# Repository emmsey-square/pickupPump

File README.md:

#   PickupPump- a Vacuum Pickup Tool for SMD Components (In Progress)

##  Brief

I was a big fan of the Pixel Pump project by Robbin's and loving the idea, but wanting to create my own version to better suit my needs, as well as allow me to design a circuit board of my own, I started working on my very own version. 

## Design Choices 

- RP2350 for the main mcu as it's a new and interesting chip from Raspberry Pi with a very solid SDK for built for both of the RP2X chips. 
- USB-C port for power & USB paired with a CH224K USB PD sink chip to request 12V for all of the motors/pumps and a switching converter to step-down the voltage for the mcu
- JST connector for connection to an additional PCB outfitted with a 3x2 array of pushbuttons, with each one having functions such as toggling the current suction state of the pump, increasing/decreasing suction strength, etc.
- There's 3 Sparkfun Qwiic/ Stemma Qt compatible JST connectors onboard to connect to an Adafruit I2C OLED as well as to allow for expansions (ie. footswitch)
- Onboard Cortex debug header for debugging & programming

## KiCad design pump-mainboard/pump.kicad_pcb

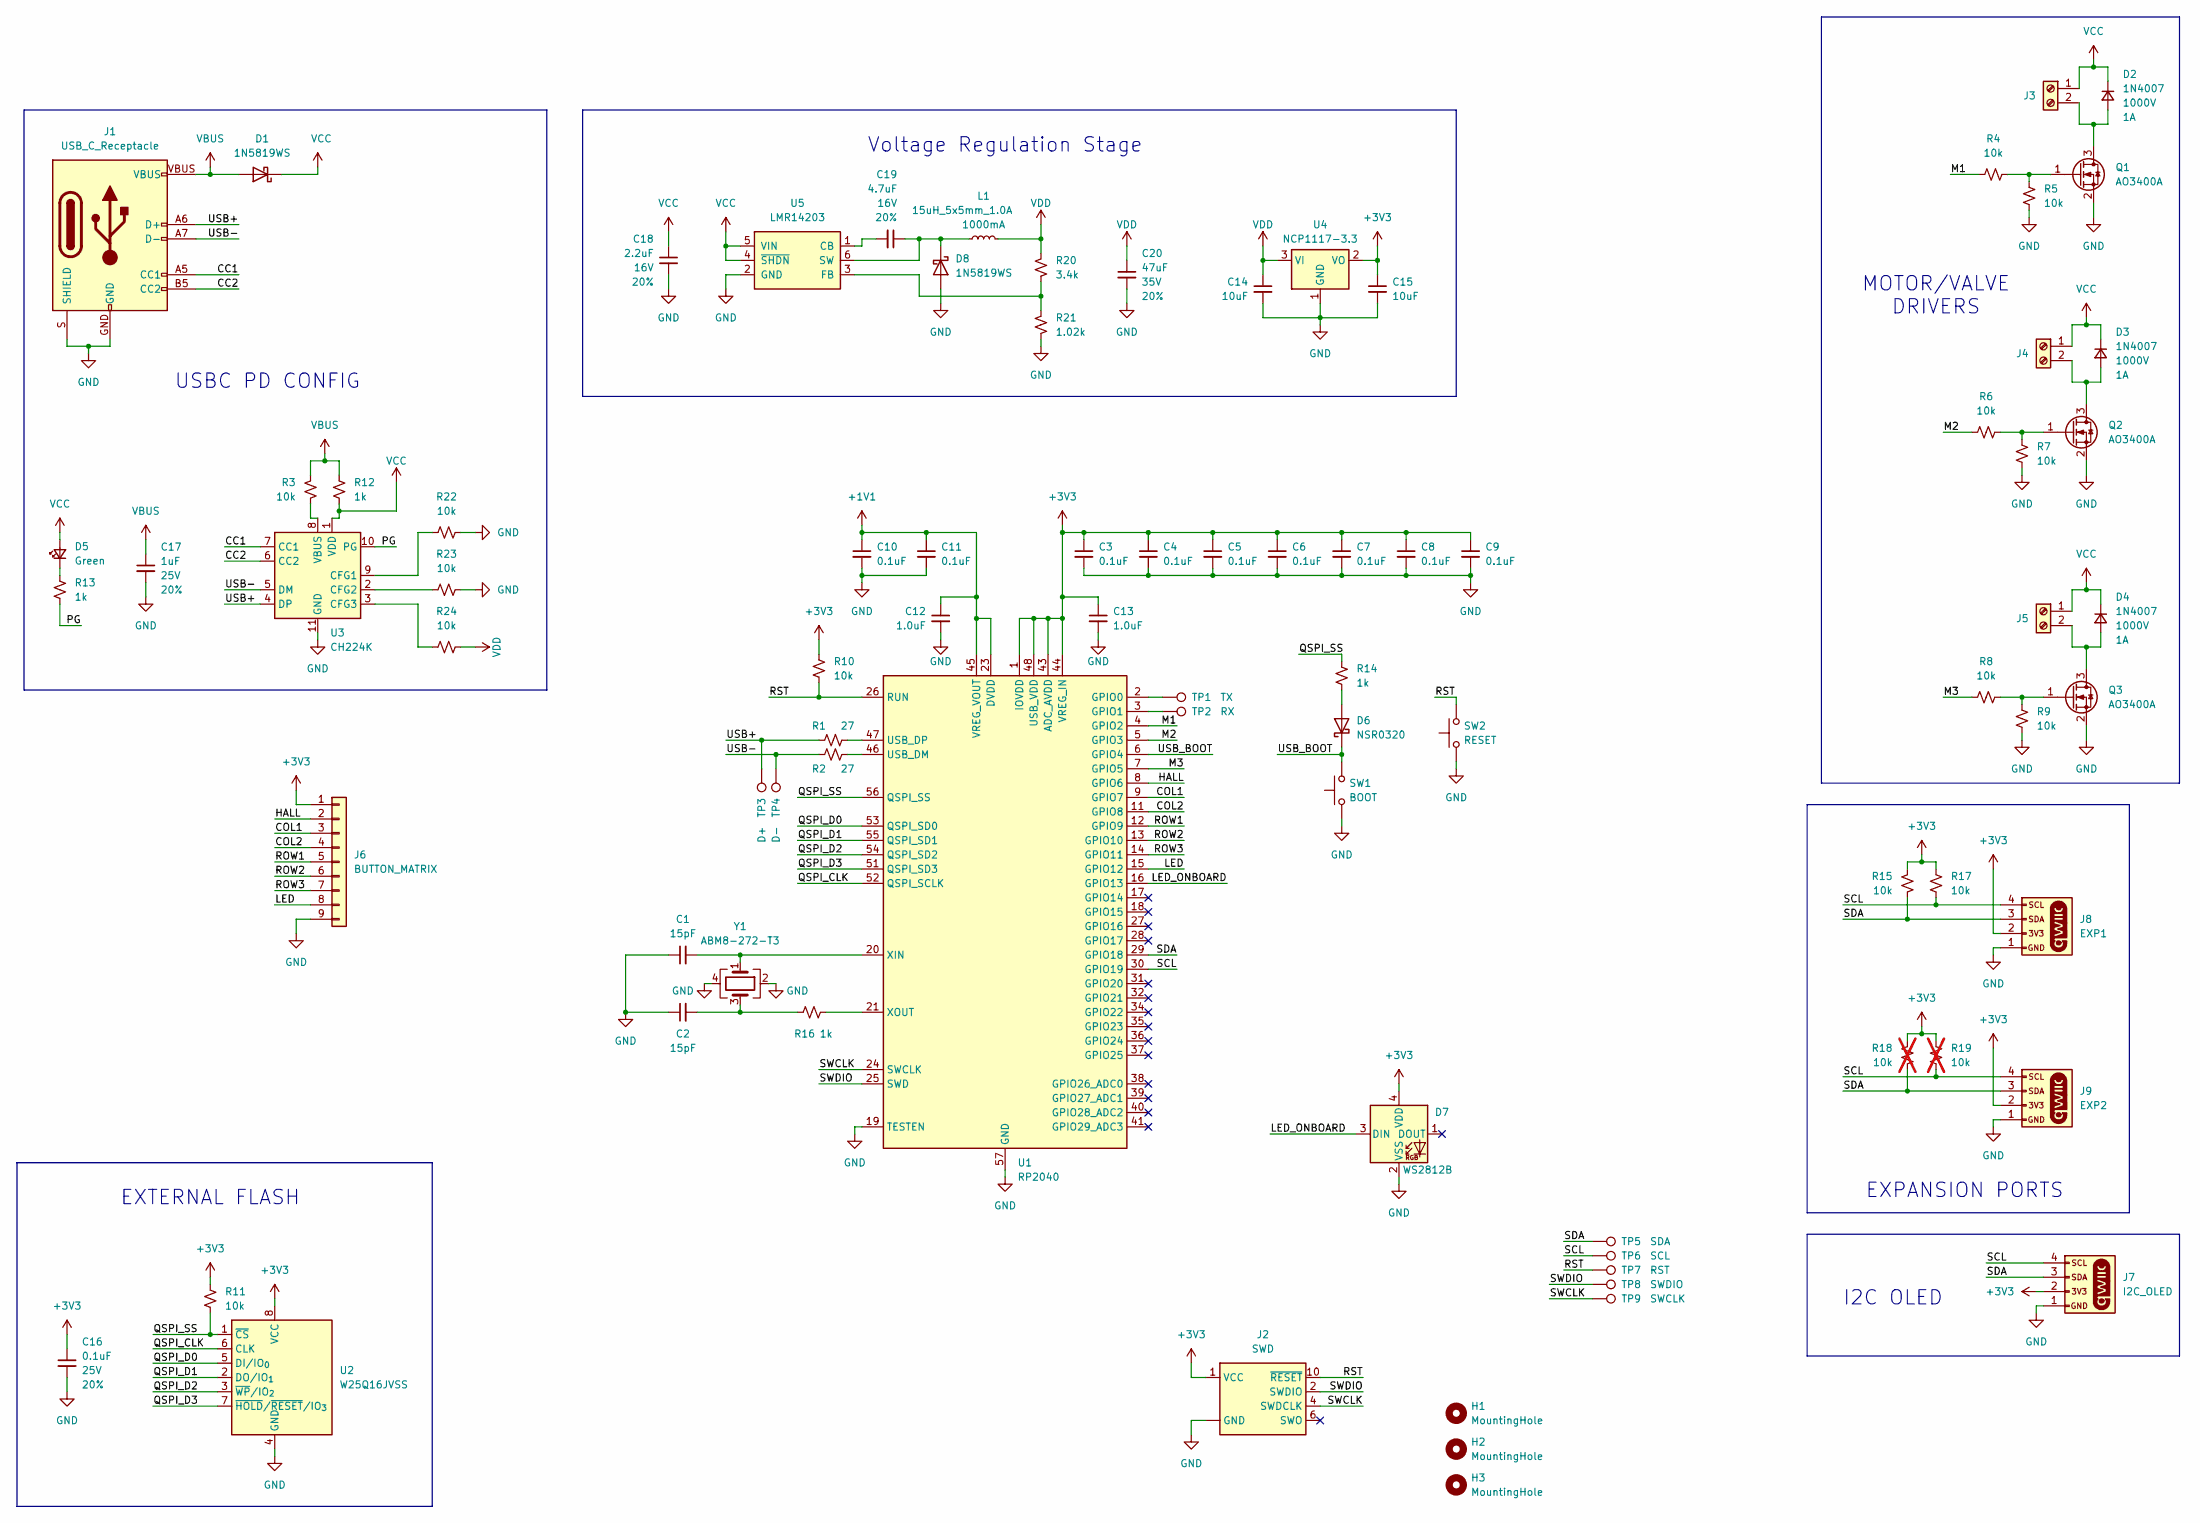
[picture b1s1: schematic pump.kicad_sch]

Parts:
C1, C2: 15pF; C_0402_1005Metric; Voltage 50V; Tolerance 5%
C3, C4, C5, C6, C7, C8, C9, C10, C11: 0.1uF; C_0402_1005Metric; Voltage 16V; Tolerance 10%
C12, C13: 1.0uF; C_0402_1005Metric; Voltage 16V; Tolerance 10%
C14, C15: 10uF; C_0603_1608Metric; Voltage 10V; Tolerance 20%
C16: 0.1uF; C_0603_1608Metric; Voltage 25V; Tolerance 20%
C17: 1uF; C_0603_1608Metric; Voltage 25V; Tolerance 20%
C18: 2.2uF; C_1206_3216Metric; Voltage 16V; Tolerance 20%
C19: 4.7uF; C_1206_3216Metric; Voltage 16V; Tolerance 20%
C20: 47uF; C_0603_1608Metric; Voltage 35V; Tolerance 20%
D1, D8: 1N5819WS; D_SOD-323_HandSoldering
D2, D3, D4: 1N4007; SOD-123
D5: Green; LED_0603_1608Metric_Green
D6: NSR0320; D_SOD-323_HandSoldering
D7: WS2812B; WS2812_2020
H1, H2, H3: MountingHole; MountingHole_3mm
J1: USB_C_Receptacle; USB-C_16
J2: SWD; 2x05_P1.27mm
J3, J4, J5: Screw_Terminal_01x02; TerminalBlock_Xinya_XY308-2.54-2P_1x02_P2.54mm_Horizontal
J6: BUTTON_MATRIX; JST_1x09_P1.25mm_Locking_Horizontal_SMD
J7: I2C_OLED; JST_1x04_P1.0mm_Vertical_SMD
J8: EXP1; JST_1x04_P1.0mm_Horizontal_SMD
J9: EXP2; JST_1x04_P1.0mm_Horizontal_SMD
L1: 15uH_5x5mm_1.0A; Inductor_4.7x4.7mm
Q1, Q2, Q3: AO3400A; SOT-23
R1, R2: 27; R_0402_1005Metric
R3, R4, R5, R6, R7, R8, R9, R10, R11: 10k; R_0603_1608Metric
R12, R13, R14: 1k; R_0603_1608Metric
R15, R17, R22, R23, R24: 10k; R_0402_1005Metric
R16: 1k; R_0402_1005Metric
R18, R19: 10k; R_0402_1005Metric; not fitted
R20: 3.4k; R_0402_1005Metric
R21: 1.02k; R_0402_1005Metric
SW1: BOOT; Push_SMD_4.2x3.2mm
SW2: RESET; Push_SMD_4.2x3.2mm
TP1: TX; TestPoint-1.25mm
TP2: RX; TestPoint-1.25mm
TP3: D+; TestPoint-1.25mm
TP4: D-; TestPoint-1.25mm
TP5: SDA; TestPoint-1.25mm
TP6: SCL; TestPoint-1.25mm
TP7: RST; TestPoint-1.25mm
TP8: SWDIO; TestPoint-1.25mm
TP9: SWCLK; TestPoint-1.25mm
U1: RP2040; QFN-56-1EP_7x7mm_P0.4mm_EP3.2x3.2mm
U2: W25Q16JVSS; SOIC-8_5.3x5.3mm_P1.27mm
U3: CH224K; SSOP-10-1EP_3.9x4.9mm_P1mm_EP2.1x3.3mm
U4: NCP1117-3.3; SOT-223-3_TabPin2
U5: LMR14203; SOT23-6
Y1: ABM8-272-T3; Crystal_SMD_EuroQuartz_MT-4Pin_3.2x2.5mm_HandSoldering

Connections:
+1V1: C10.1, C11.1, C12.1, U1.23 (DVDD), U1.45 (VREG_VOUT), U1.50 (DVDD)
+3V3: C3.1, C4.1, C5.1, C6.1, C7.1, C8.1, C9.1, C13.1, C15.1, C16.1, D7.4 (VDD), J2.1 (VCC), J6.1, J7.2, J8.2, J9.2, R10.2, R11.2, R15.2, R17.2, R18.2, R19.2, U1.1 (IOVDD), U1.10 (IOVDD), U1.22 (IOVDD), U1.33 (IOVDD), U1.42 (IOVDD), U1.43 (ADC_AVDD), U1.44 (VREG_IN), U1.48 (USB_VDD), U1.49 (IOVDD), U2.8 (VCC), U4.2 (VO)
/CC1: J1.A5 (CC1), U3.7 (CC1)
/CC2: J1.B5 (CC2), U3.6 (CC2)
/COL1: J6.3, U1.9 (GPIO7)
/COL2: J6.4, U1.11 (GPIO8)
/HALL: J6.2, U1.8 (GPIO6)
/LED: J6.8, U1.15 (GPIO12)
/LED_ONBOARD: D7.3 (DIN), U1.16 (GPIO13)
/M1: R4.1, U1.4 (GPIO2)
/M2: R6.1, U1.5 (GPIO3)
/M3: R8.1, U1.7 (GPIO5)
/PG: R13.1, U3.10 (PG)
/QSPI_CLK: U1.52 (QSPI_SCLK), U2.6 (CLK)
/QSPI_D0: U1.53 (QSPI_SD0), U2.5 (DI/IO_{0})
/QSPI_D1: U1.55 (QSPI_SD1), U2.2 (DO/IO_{1})
/QSPI_D2: U1.54 (QSPI_SD2), U2.3 (~WP/IO_{2})
/QSPI_D3: U1.51 (QSPI_SD3), U2.7 (~HOLD/~RESET/IO_{3})
/QSPI_SS: R11.1, R14.2, U1.56 (QSPI_SS), U2.1 (~CS)
/ROW1: J6.5, U1.12 (GPIO9)
/ROW2: J6.6, U1.13 (GPIO10)
/ROW3: J6.7, U1.14 (GPIO11)
/RST: J2.10 (~RESET), R10.1, SW2.2, TP7.1, U1.26 (RUN)
/SCL: J7.4, J8.4, J9.4, R17.1, R19.1, TP6.1, U1.30 (GPIO19)
/SDA: J7.3, J8.3, J9.3, R15.1, R18.1, TP5.1, U1.29 (GPIO18)
/SWCLK: J2.4 (SWDCLK), TP9.1, U1.24 (SWCLK)
/SWDIO: J2.2 (SWDIO), TP8.1, U1.25 (SWD)
/USB+: J1.A6 (D+), J1.B6 (D+), R1.1, TP3.1, U3.4 (DP)
/USB-: J1.A7 (D-), J1.B7 (D-), R2.1, TP4.1, U3.5 (DM)
/USB_BOOT: D6.1 (K), SW1.2, U1.6 (GPIO4)
GND: C1.1, C2.1, C3.2, C4.2, C5.2, C6.2, C7.2, C8.2, C9.2, C10.2, C11.2, C12.2, C13.2, C14.2, C15.2, C16.2, C17.2, C18.2, C20.2, D7.2 (VSS), D8.2 (A), J1.GND, J1.S (SHIELD), J2.3 (GND), J2.5 (GND), J2.9 (GND), J6.9, J7.1, J8.1, J9.1, Q1.2 (S), Q2.2 (S), Q3.2 (S), R5.1, R7.1, R9.1, R21.1, R22.2, R23.2, SW1.1, SW2.1, U1.19 (TESTEN), U1.57 (GND), U2.4 (GND), U3.11 (GND), U4.1 (GND), U5.2 (GND), Y1.2, Y1.4
unnamed: C2.2, R16.1, Y1.3
unnamed: D2.2 (A), J3.2, Q1.3 (D)
unnamed: D3.2 (A), J4.2, Q2.3 (D)
unnamed: D4.2 (A), J5.2, Q3.3 (D)
unnamed: D5.1 (K), R13.2
unnamed: D6.2 (A), R14.1
unnamed: C19.1, D8.1 (K), L1.1, U5.6 (SW)
unnamed: Q1.1 (G), R4.2, R5.2
unnamed: Q2.1 (G), R6.2, R7.2
unnamed: Q3.1 (G), R8.2, R9.2
unnamed: TP1.1, U1.2 (GPIO0)
unnamed: TP2.1, U1.3 (GPIO1)
unnamed: R2.2, U1.46 (USB_DM)
unnamed: R1.2, U1.47 (USB_DP)
unnamed: C1.2, U1.20 (XIN), Y1.1
unnamed: R16.2, U1.21 (XOUT)
unnamed: R22.1, U3.9 (CFG1)
unnamed: R23.1, U3.2 (CFG2)
unnamed: R24.1, U3.3 (CFG3)
unnamed: R3.1, U3.8 (VBUS)
unnamed: C19.2, U5.1 (CB)
unnamed: R20.1, R21.2, U5.3 (FB)
VBUS: C17.1, D1.2 (A), J1.VBUS, R3.2, R12.2
VCC: C18.1, D1.1 (K), D2.1 (K), D3.1 (K), D4.1 (K), D5.2 (A), J3.1, J4.1, J5.1, R12.1, U3.1 (VDD), U5.4 (~SHDN), U5.5 (VIN)
VDD: C14.1, C20.1, L1.2, R20.2, R24.2, U4.3 (VI)

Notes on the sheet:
I2C OLED
Voltage Regulation Stage
USBC PD CONFIG
EXPANSION PORTS
MOTOR/VALVE DRIVERS
EXTERNAL FLASH

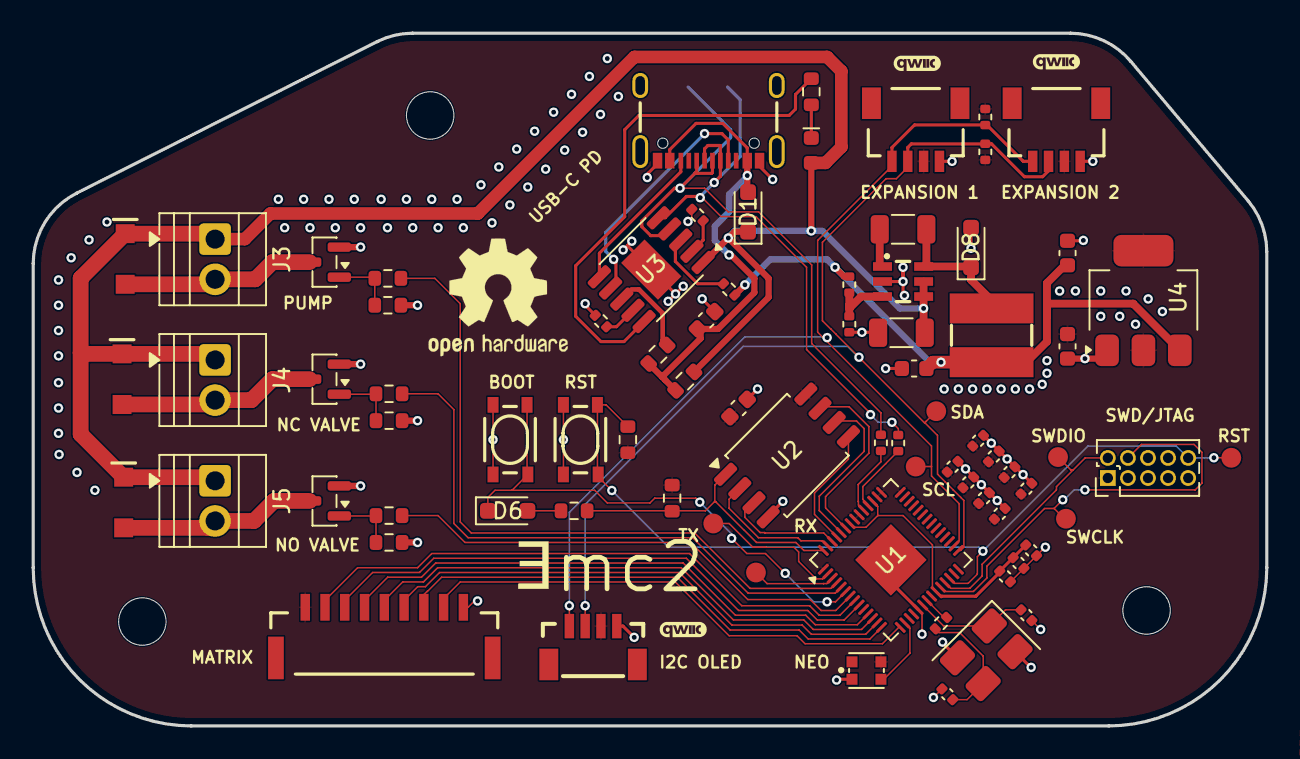
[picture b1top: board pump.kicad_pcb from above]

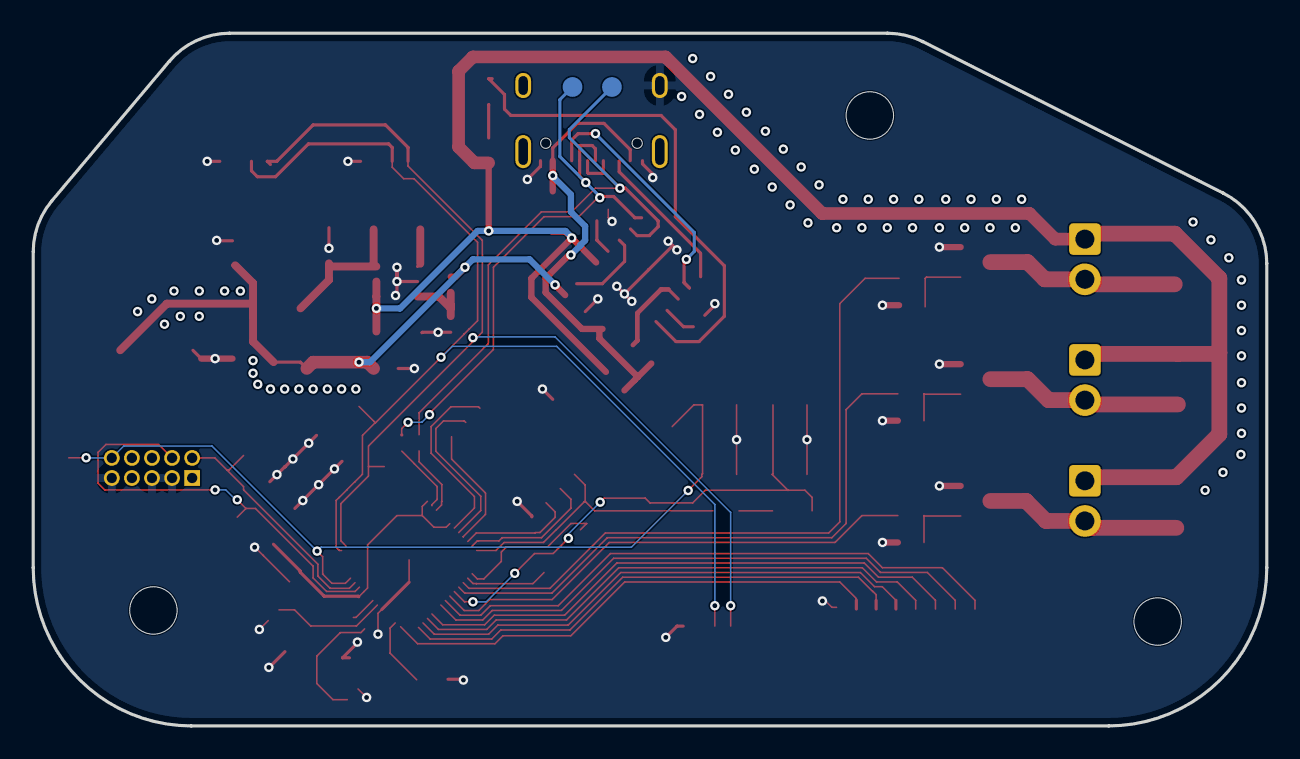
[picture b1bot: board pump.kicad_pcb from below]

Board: 2 copper layers, 78.0 x 43.8 mm, 83 parts (2 on the bottom side), 56 nets.

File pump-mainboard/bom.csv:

"Id";"Designator";"Footprint";"Quantity";"Designation";"Supplier and ref";
1;"TP5";"TestPoint-1.25mm";1;"SDA";;;
2;"C19";"C_1206_3216Metric";1;"4.7uF";;;
3;"R16";"R_0402_1005Metric";1;"1k";;;
4;"C10,C7,C8,C6,C9,C5,C4,C3,C11";"C_0402_1005Metric";9;"0.1uF";;;
5;"L1";"Inductor_4.7x4.7mm";1;"15uH_5x5mm_1.0A";;;
6;"Y1";"Crystal_SMD_EuroQuartz_MT-4Pin_3.2x2.5mm_HandSoldering";1;"ABM8-272-T3";;;
7;"TP1";"TestPoint-1.25mm";1;"TX";;;
8;"Q2,Q1,Q3";"SOT-23";3;"AO3400A";;;
9;"D1,D8";"D_SOD-323_HandSoldering";2;"1N5819WS";;;
10;"J3,J4,J5";"TerminalBlock_Xinya_XY308-2.54-2P_1x02_P2.54mm_Horizontal";3;"Screw_Terminal_01x02";;;
11;"C18";"C_1206_3216Metric";1;"2.2uF";;;
12;"D4,D3,D2";"SOD-123";3;"1N4007";;;
13;"U5";"SOT23-6";1;"LMR14203";;;
14;"C12,C13";"C_0402_1005Metric";2;"1.0uF";;;
15;"C1,C2";"C_0402_1005Metric";2;"15pF";;;
16;"R22,R23,R17,R24,R15";"R_0402_1005Metric";5;"10k";;;
17;"R9,R3,R8,R11,R7,R6,R10,R4,R5";"R_0603_1608Metric";9;"10k";;;
18;"J6";"JST_1x09_P1.25mm_Locking_Horizontal_SMD";1;"BUTTON_MATRIX";;;
19;"U2";"SOIC-8_5.3x5.3mm_P1.27mm";1;"W25Q16JVSS";;;
20;"U4";"SOT-223-3_TabPin2";1;"NCP1117-3.3";;;
21;"J7";"JST_1x04_P1.0mm_Vertical_SMD";1;"I2C_OLED";;;
22;"D5";"LED_0603_1608Metric_Green";1;"Green";;;
23;"D7";"WS2812_2020";1;"WS2812B";;;
24;"R1,R2";"R_0402_1005Metric";2;"27";;;
25;"J9";"JST_1x04_P1.0mm_Horizontal_SMD";1;"EXP2";;;
26;"SW1";"Push_SMD_4.2x3.2mm";1;"BOOT";;;
27;"D6";"D_SOD-323_HandSoldering";1;"NSR0320";;;
28;"TP7";"TestPoint-1.25mm";1;"RST";;;
29;"C20";"C_0603_1608Metric";1;"47uF";;;
30;"C14,C15";"C_0603_1608Metric";2;"10uF";;;
31;"R20";"R_0402_1005Metric";1;"3.4k";;;
32;"SW2";"Push_SMD_4.2x3.2mm";1;"RESET";;;
33;"R14,R12,R13";"R_0603_1608Metric";3;"1k";;;
34;"TP2";"TestPoint-1.25mm";1;"RX";;;
35;"C16";"C_0603_1608Metric";1;"0.1uF";;;
36;"J8";"JST_1x04_P1.0mm_Horizontal_SMD";1;"EXP1";;;
37;"U3";"SSOP-10-1EP_3.9x4.9mm_P1mm_EP2.1x3.3mm";1;"CH224K";;;
38;"R21";"R_0402_1005Metric";1;"1.02k";;;
39;"C17";"C_0603_1608Metric";1;"1uF";;;
40;"TP8";"TestPoint-1.25mm";1;"SWDIO";;;
41;"TP9";"TestPoint-1.25mm";1;"SWCLK";;;
42;"TP6";"TestPoint-1.25mm";1;"SCL";;;
43;"J2";"2x05_P1.27mm";1;"SWD";;;
44;"U1";"QFN-56-1EP_7x7mm_P0.4mm_EP3.2x3.2mm";1;"RP2040";;;
45;"J1";"USB-C_16";1;"USB_C_Receptacle";;;
46;"TP3";"TestPoint-1.25mm";1;"D+";;;
47;"TP4";"TestPoint-1.25mm";1;"D-";;;

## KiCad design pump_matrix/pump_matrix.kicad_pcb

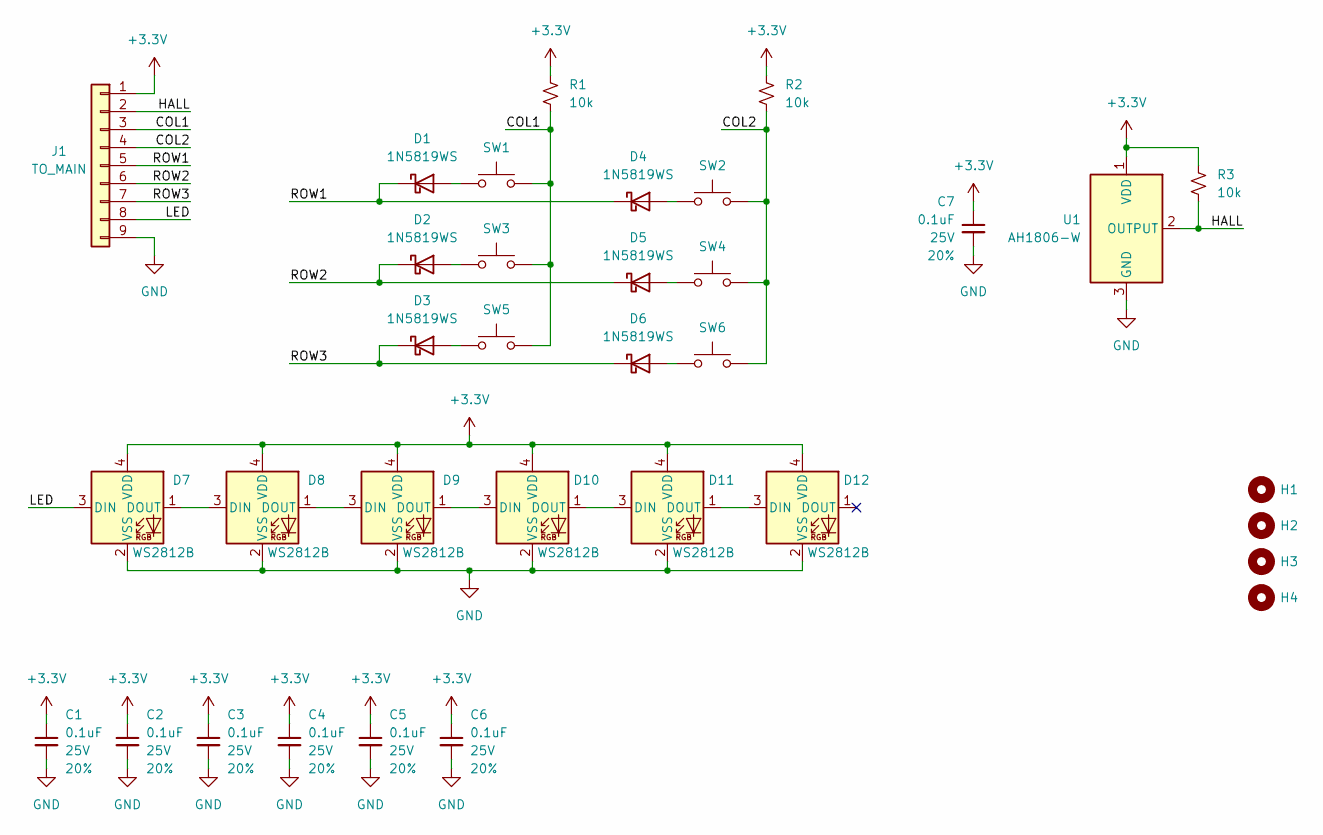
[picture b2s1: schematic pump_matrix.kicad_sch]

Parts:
C1, C2, C3, C4, C5, C6, C7: 0.1uF; C_0603_1608Metric; Voltage 25V; Tolerance 20%
D1, D2, D3, D4, D5, D6: 1N5819WS; D_SOD-323_HandSoldering
D7, D8, D9, D10, D11, D12: WS2812B; WS2812_2020
H1, H2, H3, H4: MountingHole; MountingHole_3.2mm_M3
J1: TO_MAIN; JST_1x09_P1.25mm_Locking_Horizontal_SMD
R1, R2, R3: 10k; R_0603_1608Metric
SW1, SW2, SW3, SW4, SW5, SW6: SMD_5.2x5.2mm_h2.5mm; Push_SMD_5.2x5.2mm_h2.5mm
U1: AH1806-W; SC-59

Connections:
+3.3V: C1.1, C2.1, C3.1, C4.1, C5.1, C6.1, C7.1, D7.4 (VDD), D8.4 (VDD), D9.4 (VDD), D10.4 (VDD), D11.4 (VDD), D12.4 (VDD), J1.1, R1.2, R2.2, R3.2, U1.1 (VDD)
/COL1: J1.3, R1.1, SW1.2, SW3.2, SW5.2
/COL2: J1.4, R2.1, SW2.2, SW4.2, SW6.2
/HALL: J1.2, R3.1, U1.2 (OUTPUT)
/LED: D7.3 (DIN), J1.8
/ROW1: D1.1 (K), D4.1 (K), J1.5
/ROW2: D2.1 (K), D5.1 (K), J1.6
/ROW3: D3.1 (K), D6.1 (K), J1.7
GND: C1.2, C2.2, C3.2, C4.2, C5.2, C6.2, C7.2, D7.2 (VSS), D8.2 (VSS), D9.2 (VSS), D10.2 (VSS), D11.2 (VSS), D12.2 (VSS), J1.9, U1.3 (GND)
unnamed: D1.2 (A), SW1.1
unnamed: D2.2 (A), SW3.1
unnamed: D3.2 (A), SW5.1
unnamed: D4.2 (A), SW2.1
unnamed: D5.2 (A), SW4.1
unnamed: D6.2 (A), SW6.1
unnamed: D7.1 (DOUT), D8.3 (DIN)
unnamed: D8.1 (DOUT), D9.3 (DIN)
unnamed: D9.1 (DOUT), D10.3 (DIN)
unnamed: D10.1 (DOUT), D11.3 (DIN)
unnamed: D11.1 (DOUT), D12.3 (DIN)

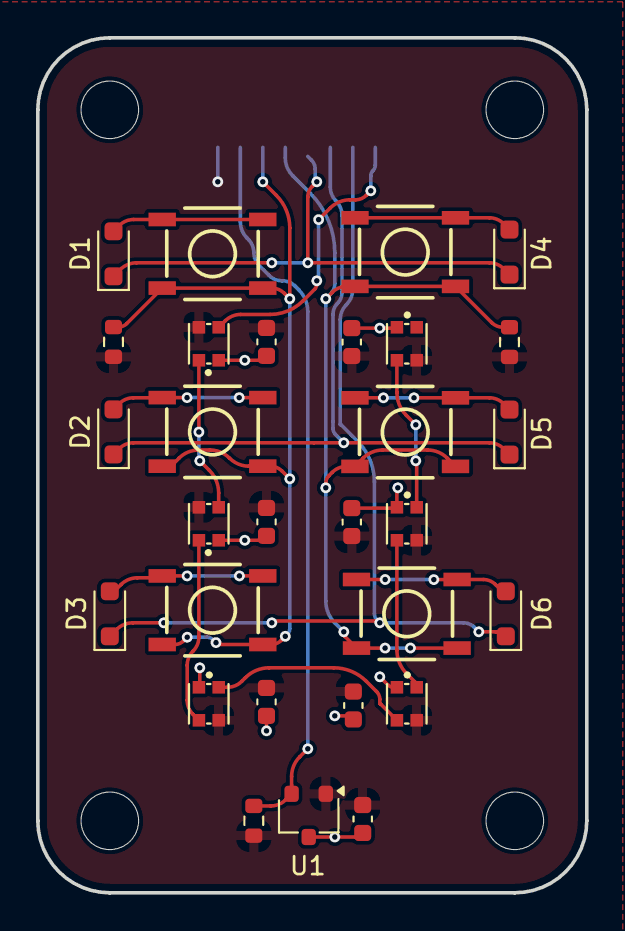
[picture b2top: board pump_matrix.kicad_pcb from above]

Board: 2 copper layers, 30.5 x 47.5 mm, 34 parts (1 on the bottom side), 20 nets.

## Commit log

2026-03-26 added pcb files for matrix pcb with switches & leds
2026-06-09 Added readme
2026-06-09 Added pickuppump image
2026-06-09 Update README.md
    Removed horizontal rule from the README.
